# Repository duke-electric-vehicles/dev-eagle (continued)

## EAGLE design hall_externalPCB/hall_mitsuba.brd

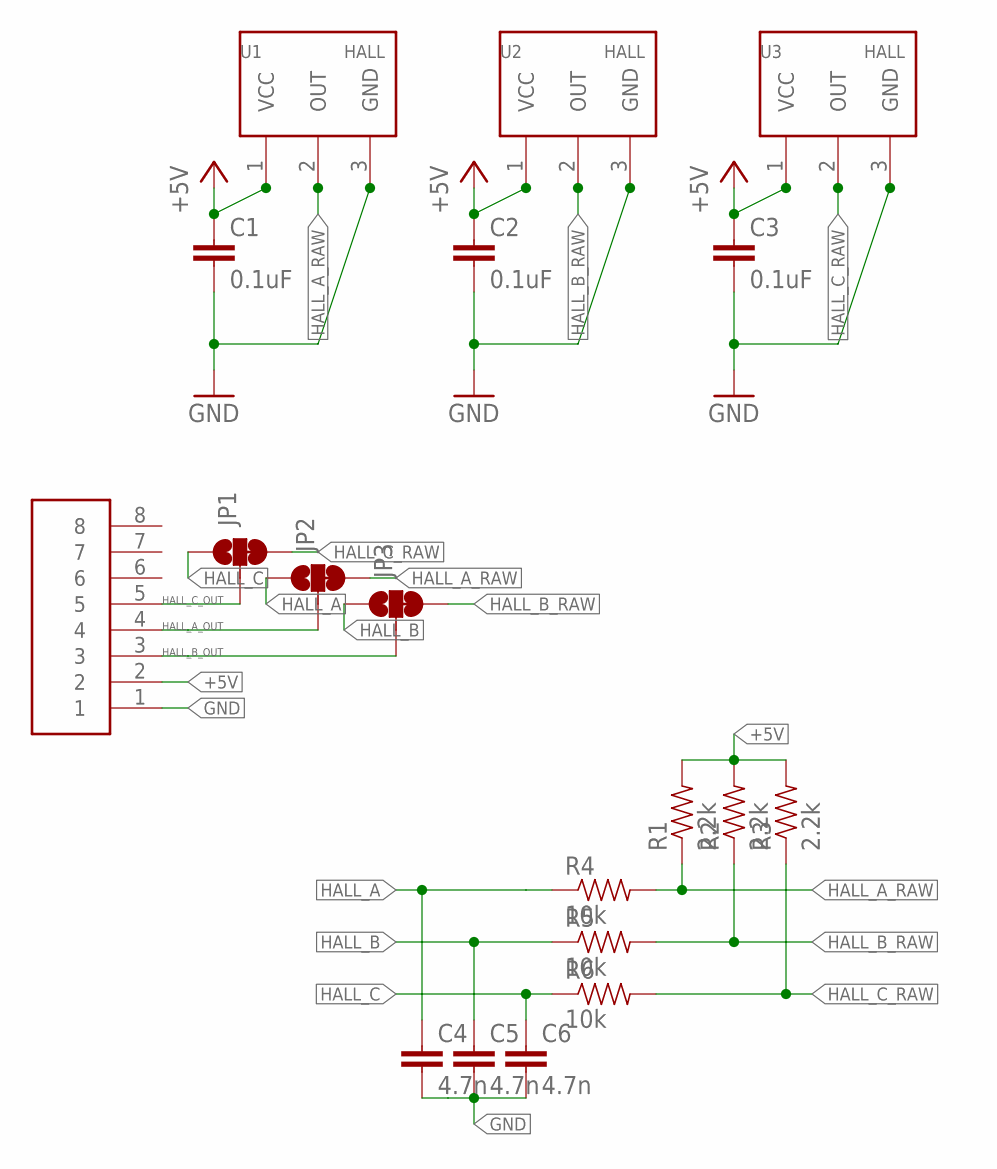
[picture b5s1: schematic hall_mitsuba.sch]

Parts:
C1, C2, C3: 0.1uF; 0603-CAP
C4, C5, C6: 4.7n; 0603-CAP
JP1, JP2, JP3: JUMPER-SMT_3_1-NC_TRACE_SILK; SMT-JUMPER_3_1-NC_TRACE_SILK
R1, R2, R3: 2.2k; 0603-RES
R4, R5, R6: 10k; 0603-RES
U1, U2, U3: HALL_SOT23W; SOT23W
U$1: HEADER8DEFAULT; 8PINVALULOK

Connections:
+5V: C1.1, C2.1, C3.1, R1.2, R2.2, R3.2, U1.1 (VCC), U2.1 (VCC), U3.1 (VCC), U$1.2
GND: C1.2, C2.2, C3.2, C4.2, C5.2, C6.2, U1.3 (GND), U2.3 (GND), U3.3 (GND), U$1.1
HALL_A: C4.1, JP2.1, R4.1
HALL_A_OUT: JP2.2, U$1.4
HALL_A_RAW: JP2.3, R1.1, R4.2, U1.2 (OUT)
HALL_B: C5.1, JP3.1, R5.1
HALL_B_OUT: JP3.2, U$1.3
HALL_B_RAW: JP3.3, R2.1, R5.2, U2.2 (OUT)
HALL_C: C6.1, JP1.1, R6.1
HALL_C_OUT: JP1.2, U$1.5
HALL_C_RAW: JP1.3, R3.1, R6.2, U3.2 (OUT)

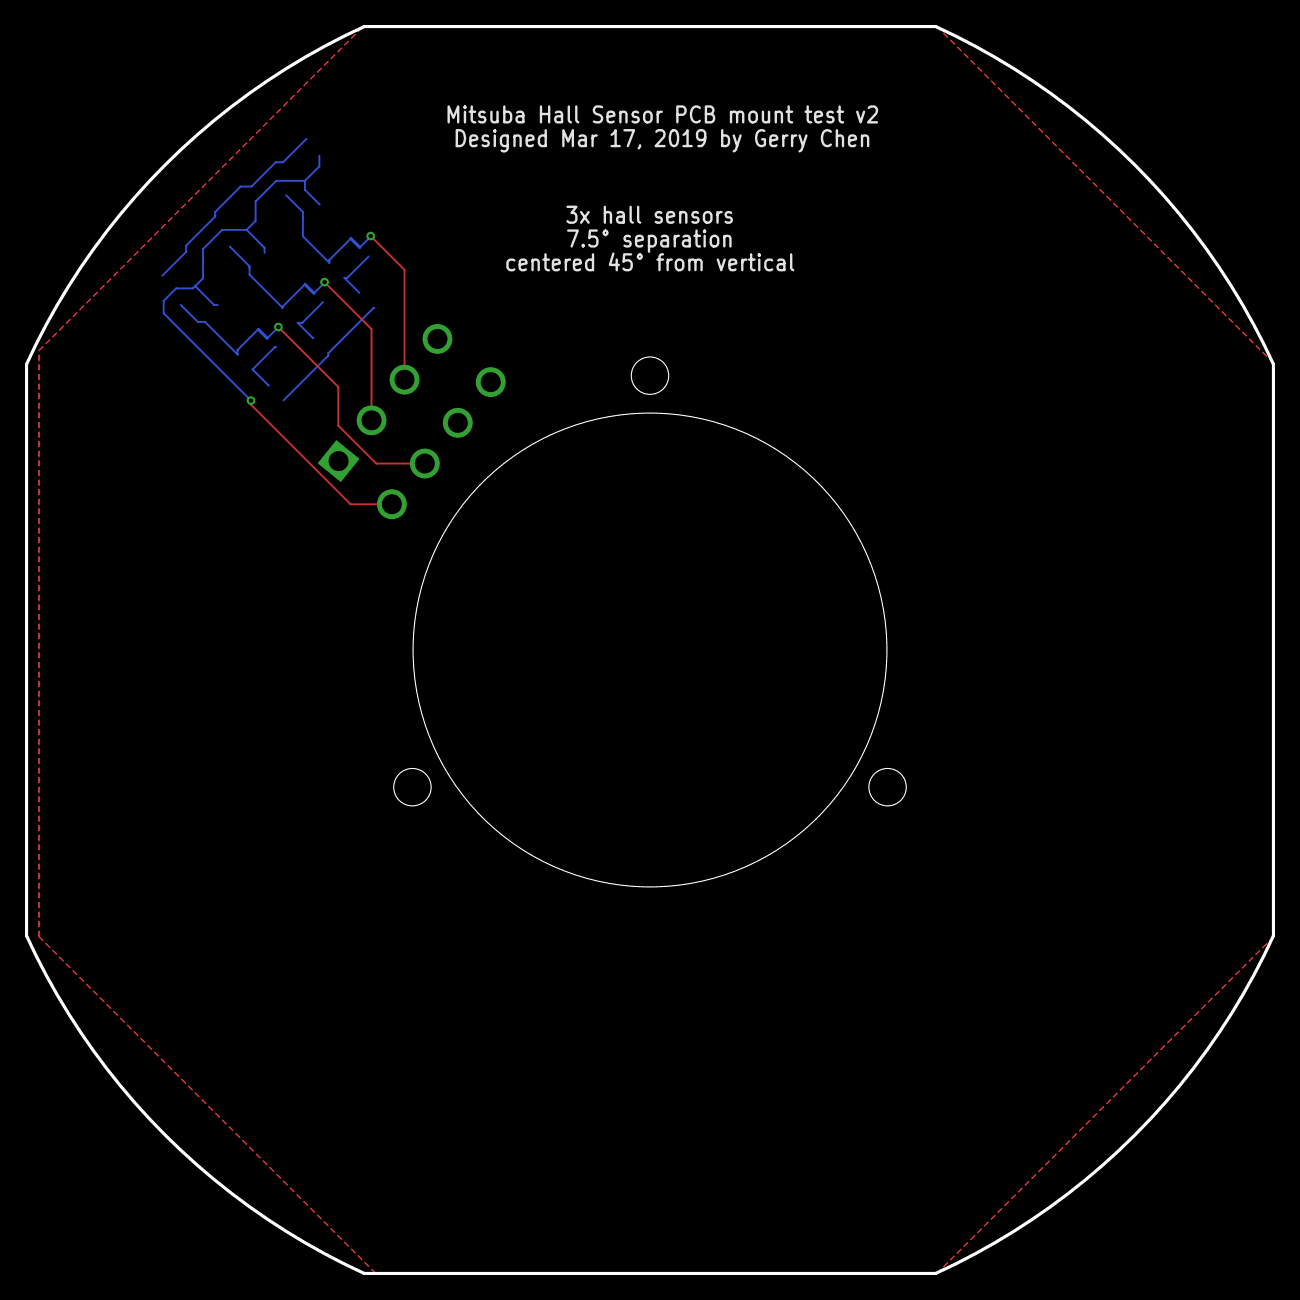
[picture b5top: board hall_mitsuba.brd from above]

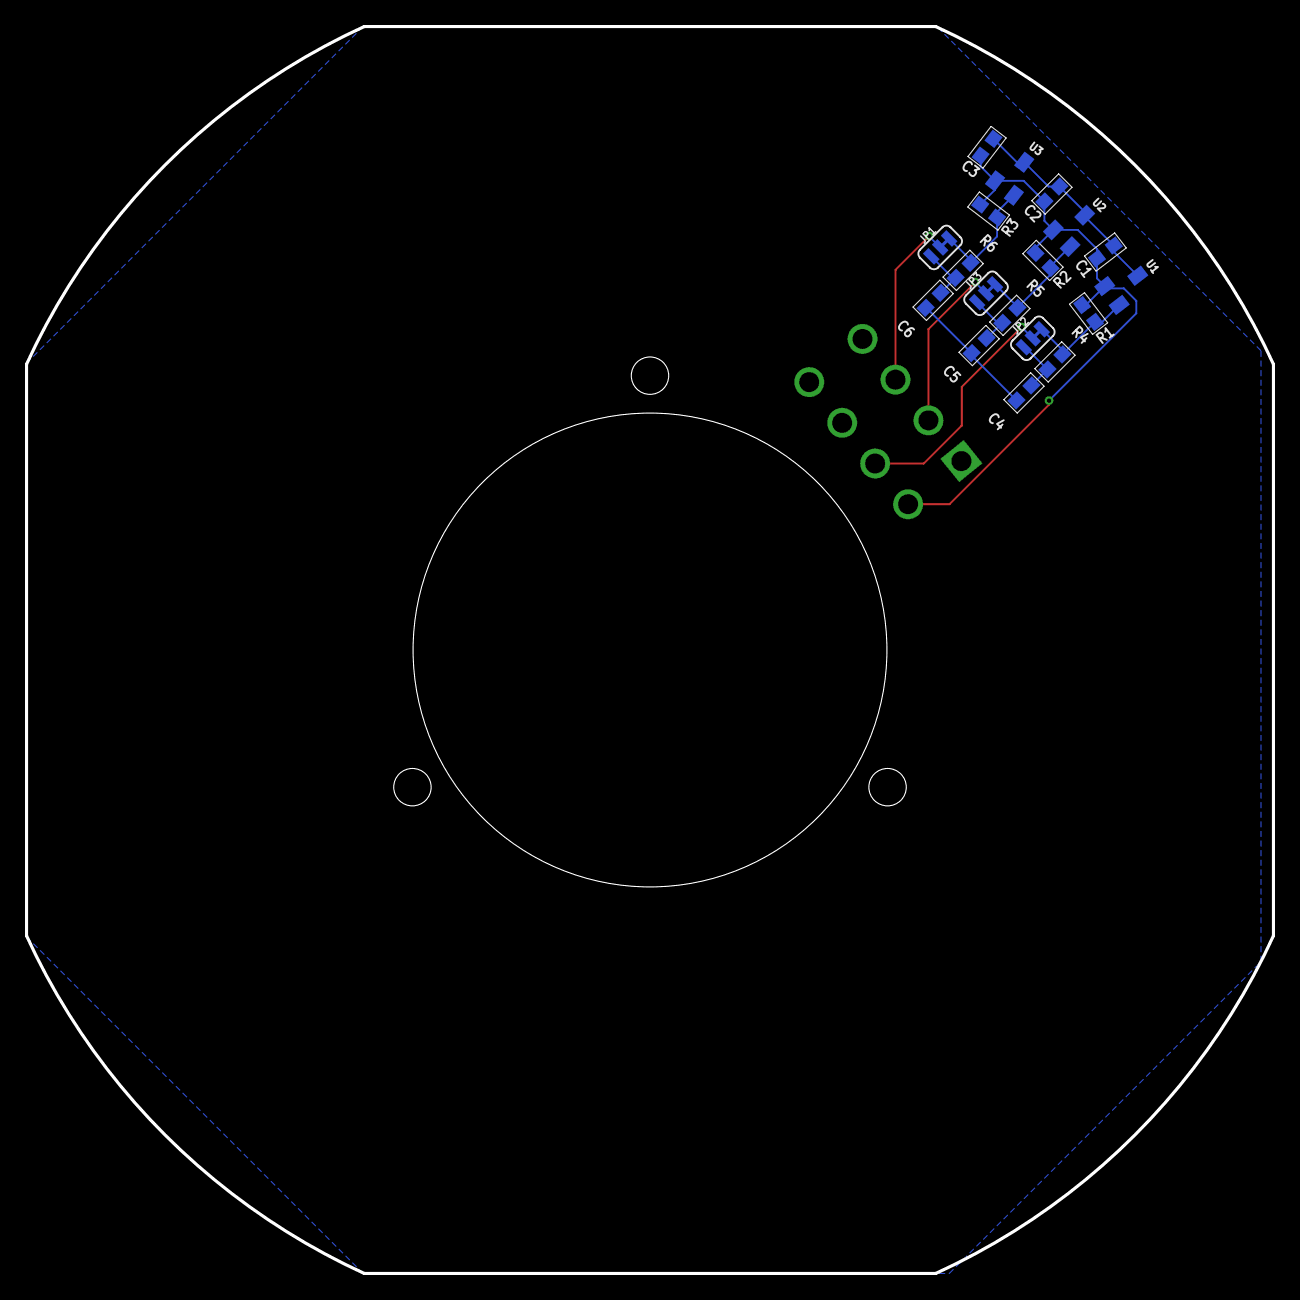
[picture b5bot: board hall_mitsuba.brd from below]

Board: 2 copper layers, 100.0 x 100.0 mm, 21 parts (18 on the bottom side), 11 nets.

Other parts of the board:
U$2, U$3: DEV

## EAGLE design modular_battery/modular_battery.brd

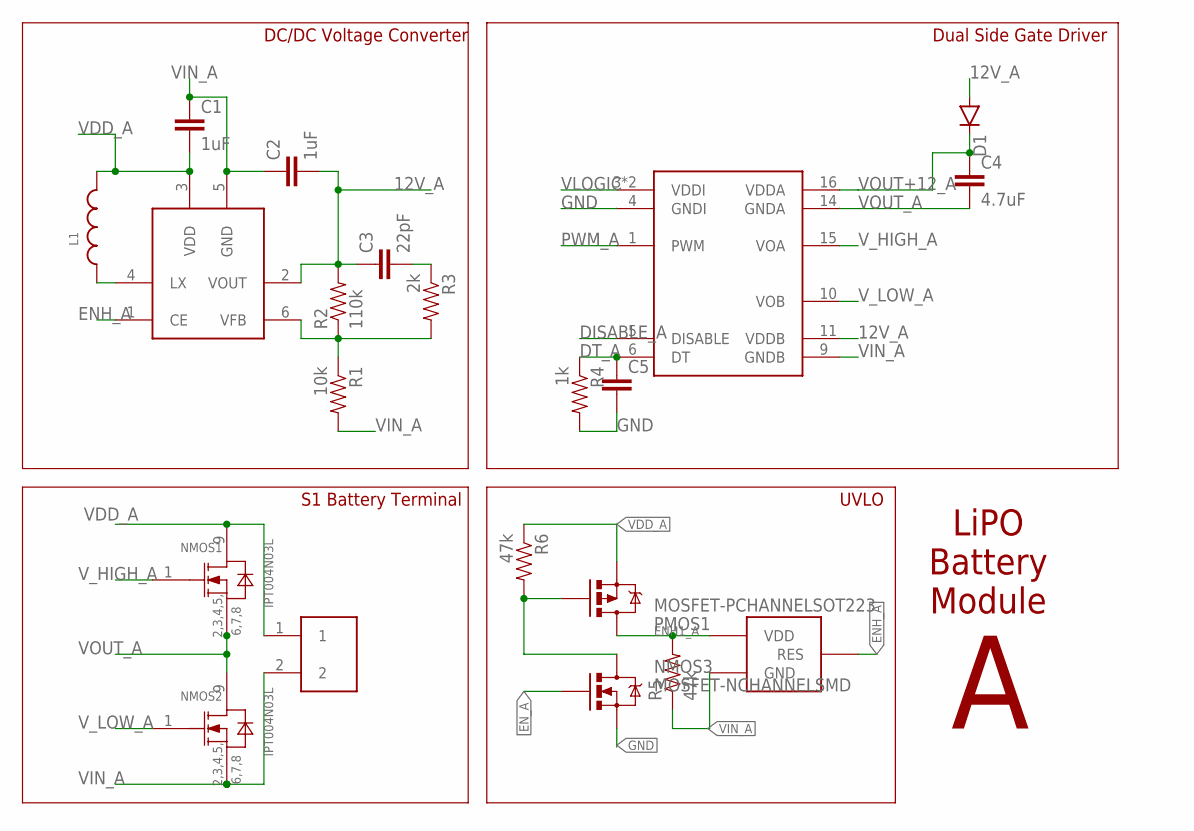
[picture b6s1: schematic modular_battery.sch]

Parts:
C1, C2: 1uF; 0603-CAP
C3: 22pF; 0603-CAP
C4: 4.7uF; 0603-CAP
C5: CAP0603-CAP; 0603-CAP
D1: DIODESMB; SMB-DIODE
DRIVER1: SI8231SOIC16W; SOIC16LWB
L1: WE-LQS_4025_74404043220A; WE-LQS_4025
NMOS1, NMOS2: IPT004N03L; INF-PG-HSOF-8-1-0
NMOS3: MOSFET-NCHANNELSMD; SOT23-3
PMOS1: MOSFET-PCHANNELSOT223; SOT223
R1: 10k; 0603-RES
R2: 110k; 0603-RES
R3: 2k; 0603-RES
R4: 1k; 0603-RES
R5, R6: 47k; 0603-RES
U$3: HEADER2; 2PINVALULOK
VDETECTOR1: BD49XXK__G; SOT23-3
VREG1: R1200SOT-23-6; SOT-23-6

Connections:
12V_A: C2.2, C3.1, D1.A, DRIVER1.11 (VDDB), R2.2, VREG1.2 (VOUT)
DISABLE_A: DRIVER1.5 (DISABLE)
DT_A: C5.1, DRIVER1.6 (DT), R4.1
ENH1_A: PMOS1.2 (D), PMOS1.4 (D), R5.2, VDETECTOR1.3 (VDD)
ENH_A: VDETECTOR1.2 (RES), VREG1.1 (CE)
EN_A: NMOS3.1 (G)
GND: C5.2, DRIVER1.4 (GNDI), NMOS3.2 (S), R4.2
unnamed: L1.1, VREG1.4 (LX)
unnamed: R1.1, R2.1, R3.2, VREG1.6 (VFB)
unnamed: C3.2, R3.1
unnamed: NMOS3.3 (D), PMOS1.1 (G), R6.2
PWM_A: DRIVER1.1 (PWM)
VDD_A: C1.2, L1.2, NMOS1.9, PMOS1.3 (S), R6.1, U$3.1, VREG1.3 (VDD)
VIN_A: C1.1, C2.1, DRIVER1.9 (GNDB), NMOS2.2, NMOS2.3, NMOS2.4, NMOS2.5, NMOS2.6, NMOS2.7, NMOS2.8, R1.2, R5.1, U$3.2, VDETECTOR1.1 (GND), VREG1.5 (GND)
VLOGIC: DRIVER1.3 (VDDI), DRIVER1.8 (VDDI)
VOUT+12_A: C4.1, D1.C, DRIVER1.16 (VDDA)
VOUT_A: C4.2, DRIVER1.14 (GNDA), NMOS1.2, NMOS1.3, NMOS1.4, NMOS1.5, NMOS1.6, NMOS1.7, NMOS1.8, NMOS2.9
V_HIGH_A: DRIVER1.15 (VOA), NMOS1.1
V_LOW_A: DRIVER1.10 (VOB), NMOS2.1

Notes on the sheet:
DC/DC Voltage Converter
S1 Battery Terminal
Dual Side Gate Driver
LiPO Battery Module
UVLO

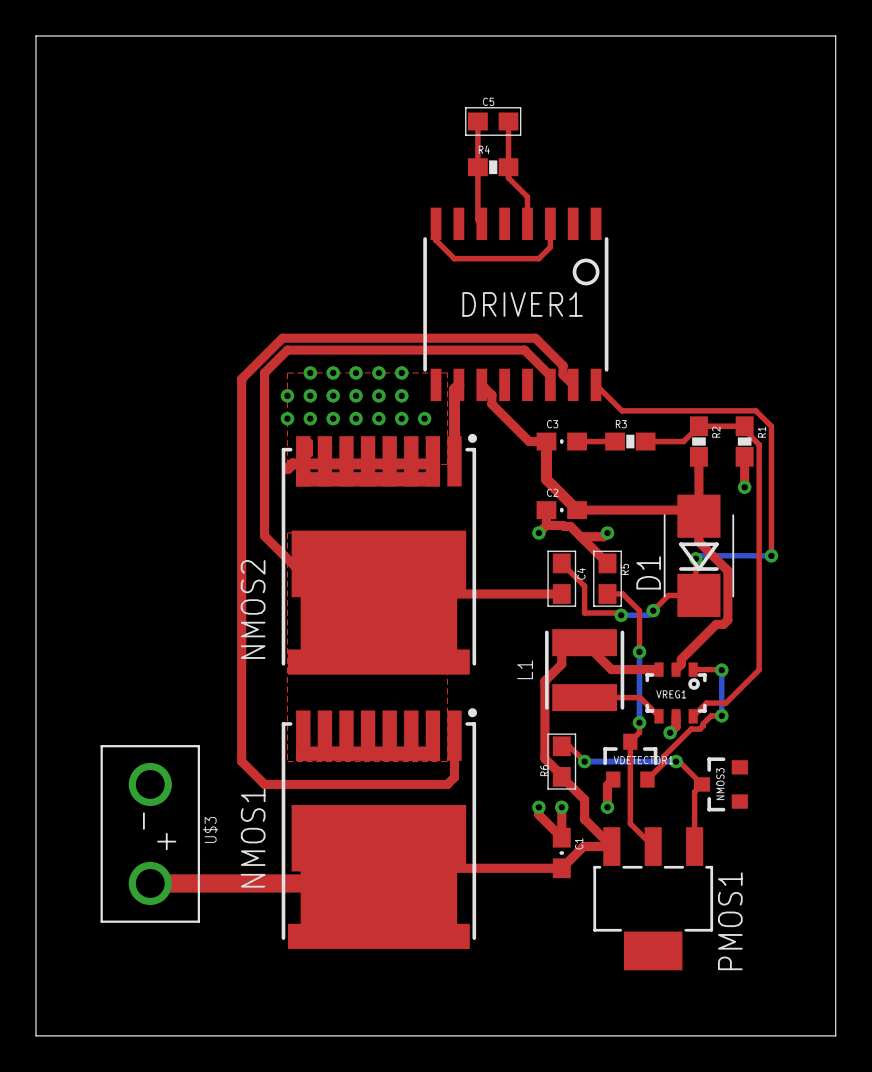
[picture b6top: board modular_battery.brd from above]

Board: 2 copper layers, 44.4 x 55.6 mm, 21 parts (0 on the bottom side), 16 nets.

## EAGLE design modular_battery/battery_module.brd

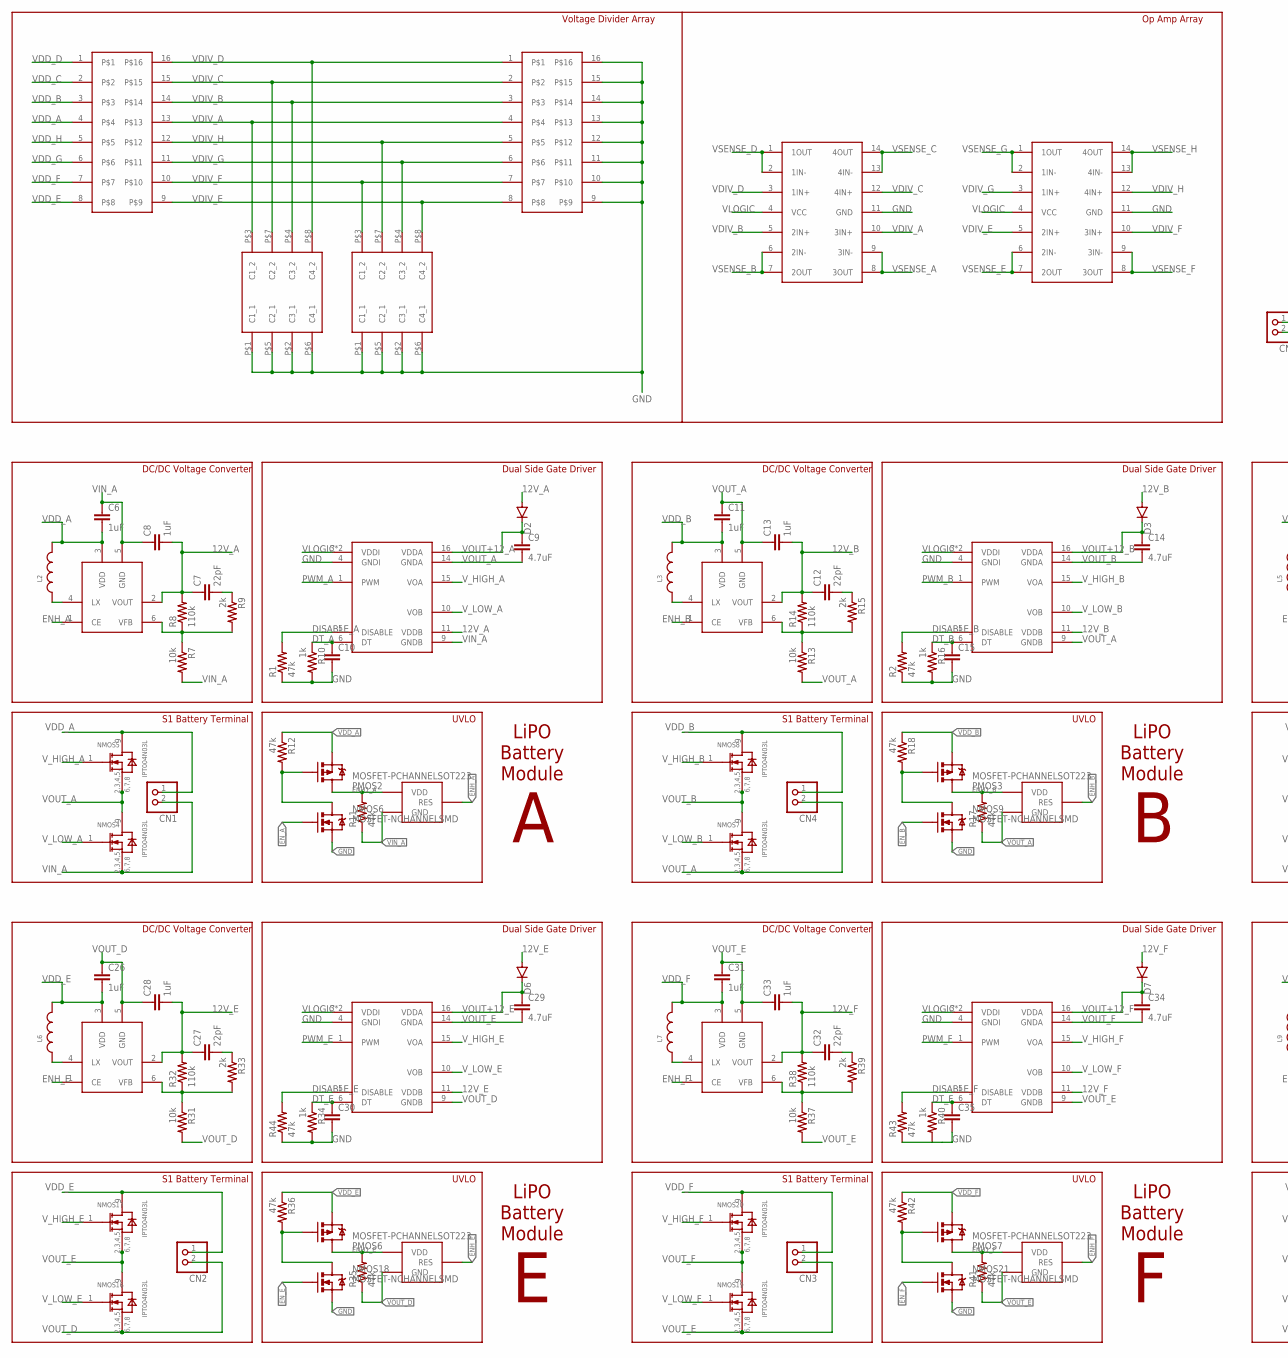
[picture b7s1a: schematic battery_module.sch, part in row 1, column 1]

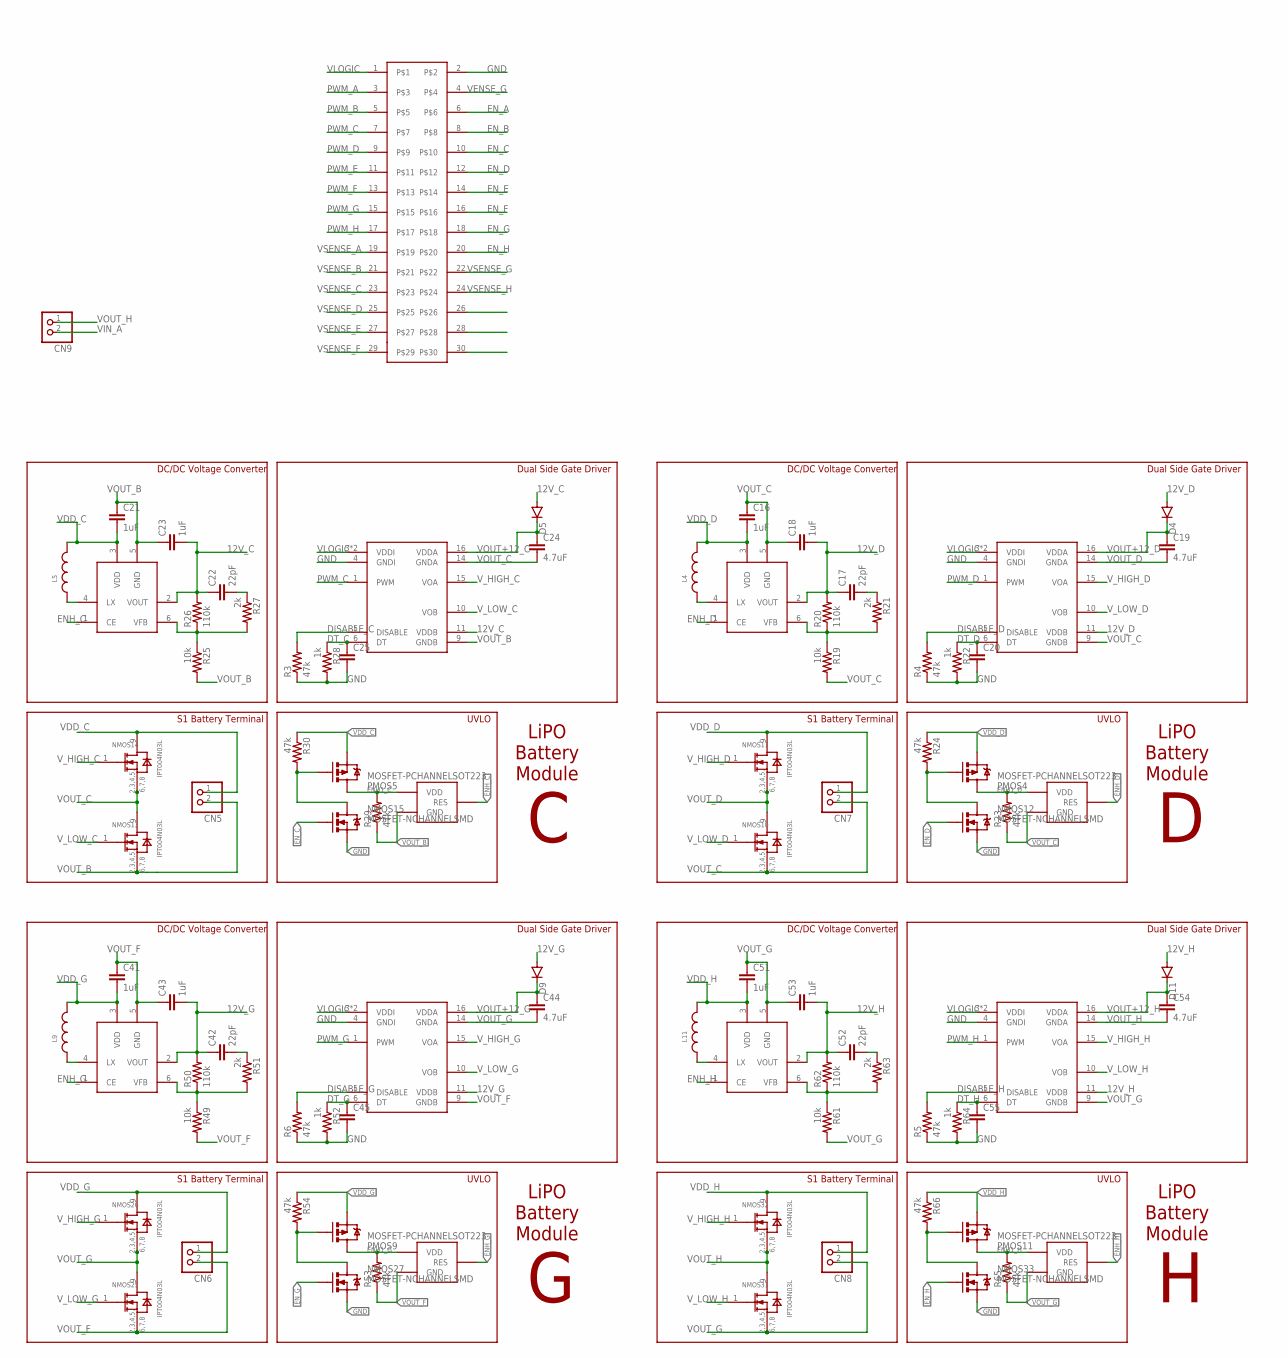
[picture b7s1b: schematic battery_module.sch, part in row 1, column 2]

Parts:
ARRAY1: 47k; 1506
ARRAY2: EXB-2HV; 1506
C6, C8, C11, C13, C16, C18, C21, C23, C26, C28, C31, C33, C41, C43, C51, C53: 1uF; 0603-CAP
C7, C12, C17, C22, C27, C32, C42, C52: 22pF; 0603-CAP
C9, C14, C19, C24, C29, C34, C44, C54: 4.7uF; 0603-CAP
C10, C15, C20, C25, C30, C35, C45, C55: CAP0603-CAP; 0603-CAP
CN1, CN2, CN3, CN4, CN5, CN6, CN7, CN8, CN9: JST_2PIN-THM; JST-PH-2-THM
D2, D3, D4, D5, D6, D7, D9, D11: DIODESMB; SMB-DIODE
DRIVER2, DRIVER3, DRIVER4, DRIVER5, DRIVER6, DRIVER7, DRIVER9, DRIVER11: SI8231SOIC16W; SOIC16LWB
L2, L3, L4, L5, L6, L7, L9, L11: WE-LQS_4025_74404043220A; WE-LQS_4025
NMOS4, NMOS5, NMOS7, NMOS8, NMOS10, NMOS11, NMOS13, NMOS14, NMOS16, NMOS17, NMOS19, NMOS20, NMOS25, NMOS26, NMOS31, NMOS32: IPT004N03L; INF-PG-HSOF-8-1-0
NMOS6, NMOS9, NMOS12, NMOS15, NMOS18, NMOS21, NMOS27, NMOS33: MOSFET-NCHANNELSMD; SOT23-3
PMOS2, PMOS3, PMOS4, PMOS5, PMOS6, PMOS7, PMOS9, PMOS11: MOSFET-PCHANNELSOT223; SOT223
R1, R2, R3, R4, R5, R6, R11, R12, R17, R18, R23, R24, R29, R30, R35, R36, R41, R42, R43, R44, R53, R54, R65, R66: 47k; 0603-RES
R7, R13, R19, R25, R31, R37, R49, R61: 10k; 0603-RES
R8, R14, R20, R26, R32, R38, R50, R62: 110k; 0603-RES
R9, R15, R21, R27, R33, R39, R51, R63: 2k; 0603-RES
R10, R16, R22, R28, R34, R40, R52, R64: 1k; 0603-RES
U$1: 30_HEADER; 2X15_SHROUDED
U$10, U$12: LM324; SOIC14
U$11, U$13: CL31; 1206-4XARRAY
VDETECTOR2, VDETECTOR3, VDETECTOR4, VDETECTOR5, VDETECTOR6, VDETECTOR7, VDETECTOR9, VDETECTOR11: BD49XXK__G; SOT23-3
VREG2, VREG3, VREG4, VREG5, VREG6, VREG7, VREG9, VREG11: R1200SOT-23-6; SOT-23-6

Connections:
12V_A: C7.1, C8.2, D2.A, DRIVER2.11 (VDDB), R8.2, VREG2.2 (VOUT)
12V_B: C12.1, C13.2, D3.A, DRIVER3.11 (VDDB), R14.2, VREG3.2 (VOUT)
12V_C: C22.1, C23.2, D5.A, DRIVER5.11 (VDDB), R26.2, VREG5.2 (VOUT)
12V_D: C17.1, C18.2, D4.A, DRIVER4.11 (VDDB), R20.2, VREG4.2 (VOUT)
12V_E: C27.1, C28.2, D6.A, DRIVER6.11 (VDDB), R32.2, VREG6.2 (VOUT)
12V_F: C32.1, C33.2, D7.A, DRIVER7.11 (VDDB), R38.2, VREG7.2 (VOUT)
12V_G: C42.1, C43.2, D9.A, DRIVER9.11 (VDDB), R50.2, VREG9.2 (VOUT)
12V_H: C52.1, C53.2, D11.A, DRIVER11.11 (VDDB), R62.2, VREG11.2 (VOUT)
DISABLE_A: DRIVER2.5 (DISABLE), R1.2
DISABLE_B: DRIVER3.5 (DISABLE), R2.2
DISABLE_C: DRIVER5.5 (DISABLE), R3.2
DISABLE_D: DRIVER4.5 (DISABLE), R4.2
DISABLE_E: DRIVER6.5 (DISABLE), R44.2
DISABLE_F: DRIVER7.5 (DISABLE), R43.2
DISABLE_G: DRIVER9.5 (DISABLE), R6.2
DISABLE_H: DRIVER11.5 (DISABLE), R5.2
DT_A: C10.1, DRIVER2.6 (DT), R10.1
DT_B: C15.1, DRIVER3.6 (DT), R16.1
DT_C: C25.1, DRIVER5.6 (DT), R28.1
DT_D: C20.1, DRIVER4.6 (DT), R22.1
DT_E: C30.1, DRIVER6.6 (DT), R34.1
DT_F: C35.1, DRIVER7.6 (DT), R40.1
DT_G: C45.1, DRIVER9.6 (DT), R52.1
DT_H: C55.1, DRIVER11.6 (DT), R64.1
ENH1_A: PMOS2.2 (D), PMOS2.4 (D), R11.2, VDETECTOR2.3 (VDD)
ENH1_B: PMOS3.2 (D), PMOS3.4 (D), R17.2, VDETECTOR3.3 (VDD)
ENH1_C: PMOS5.2 (D), PMOS5.4 (D), R29.2, VDETECTOR5.3 (VDD)
ENH1_D: PMOS4.2 (D), PMOS4.4 (D), R23.2, VDETECTOR4.3 (VDD)
ENH1_E: PMOS6.2 (D), PMOS6.4 (D), R35.2, VDETECTOR6.3 (VDD)
ENH1_F: PMOS7.2 (D), PMOS7.4 (D), R41.2, VDETECTOR7.3 (VDD)
ENH1_G: PMOS9.2 (D), PMOS9.4 (D), R53.2, VDETECTOR9.3 (VDD)
ENH1_H: PMOS11.2 (D), PMOS11.4 (D), R65.2, VDETECTOR11.3 (VDD)
ENH_A: VDETECTOR2.2 (RES), VREG2.1 (CE)
ENH_B: VDETECTOR3.2 (RES), VREG3.1 (CE)
ENH_C: VDETECTOR5.2 (RES), VREG5.1 (CE)
ENH_D: VDETECTOR4.2 (RES), VREG4.1 (CE)
ENH_E: VDETECTOR6.2 (RES), VREG6.1 (CE)
ENH_F: VDETECTOR7.2 (RES), VREG7.1 (CE)
ENH_G: VDETECTOR9.2 (RES), VREG9.1 (CE)
ENH_H: VDETECTOR11.2 (RES), VREG11.1 (CE)
EN_A: NMOS6.1 (G), U$1.6
EN_B: NMOS9.1 (G), U$1.8
EN_C: NMOS15.1 (G), U$1.10
EN_D: NMOS12.1 (G), U$1.12
EN_E: NMOS18.1 (G), U$1.14
EN_F: NMOS21.1 (G), U$1.16
EN_G: NMOS27.1 (G), U$1.18
EN_H: NMOS33.1 (G), U$1.20
GND: ARRAY2.9, ARRAY2.10, ARRAY2.11, ARRAY2.12, ARRAY2.13, ARRAY2.14, ARRAY2.15, ARRAY2.16, C10.2, C15.2, C20.2, C25.2, C30.2, C35.2, C45.2, C55.2, DRIVER2.4 (GNDI), DRIVER3.4 (GNDI), DRIVER4.4 (GNDI), DRIVER5.4 (GNDI), DRIVER6.4 (GNDI), DRIVER7.4 (GNDI), DRIVER9.4 (GNDI), DRIVER11.4 (GNDI), NMOS6.2 (S), NMOS9.2 (S), NMOS12.2 (S), NMOS15.2 (S), NMOS18.2 (S), NMOS21.2 (S), NMOS27.2 (S), NMOS33.2 (S), R1.1, R2.1, R3.1, R4.1, R5.1, R6.1, R10.2, R16.2, R22.2, R28.2, R34.2, R40.2, R43.1, R44.1, R52.2, R64.2, U$1.2, U$10.11 (GND), U$11.P$1 (C1_1), U$11.P$2 (C3_1), U$11.P$5 (C2_1), U$11.P$6 (C4_1), U$12.11 (GND), U$13.P$1 (C1_1), U$13.P$2 (C3_1), U$13.P$5 (C2_1), U$13.P$6 (C4_1)
unnamed: R7.1, R8.1, R9.2, VREG2.6 (VFB)
unnamed: L2.1, VREG2.4 (LX)
unnamed: C7.2, R9.1
unnamed: NMOS6.3 (D), PMOS2.1 (G), R12.2
unnamed: R13.1, R14.1, R15.2, VREG3.6 (VFB)
unnamed: L3.1, VREG3.4 (LX)
unnamed: C12.2, R15.1
unnamed: NMOS9.3 (D), PMOS3.1 (G), R18.2
unnamed: R19.1, R20.1, R21.2, VREG4.6 (VFB)
unnamed: L4.1, VREG4.4 (LX)
unnamed: C17.2, R21.1
unnamed: NMOS12.3 (D), PMOS4.1 (G), R24.2
unnamed: R25.1, R26.1, R27.2, VREG5.6 (VFB)
unnamed: L5.1, VREG5.4 (LX)
unnamed: C22.2, R27.1
unnamed: NMOS15.3 (D), PMOS5.1 (G), R30.2
unnamed: R31.1, R32.1, R33.2, VREG6.6 (VFB)
unnamed: L6.1, VREG6.4 (LX)
unnamed: C27.2, R33.1
unnamed: NMOS18.3 (D), PMOS6.1 (G), R36.2
unnamed: R37.1, R38.1, R39.2, VREG7.6 (VFB)
unnamed: L7.1, VREG7.4 (LX)
unnamed: C32.2, R39.1
unnamed: NMOS21.3 (D), PMOS7.1 (G), R42.2
unnamed: R49.1, R50.1, R51.2, VREG9.6 (VFB)
unnamed: L9.1, VREG9.4 (LX)
unnamed: C42.2, R51.1
unnamed: NMOS27.3 (D), PMOS9.1 (G), R54.2
unnamed: R61.1, R62.1, R63.2, VREG11.6 (VFB)
unnamed: L11.1, VREG11.4 (LX)
unnamed: C52.2, R63.1
unnamed: NMOS33.3 (D), PMOS11.1 (G), R66.2
PWM_A: DRIVER2.1 (PWM), U$1.3
PWM_B: DRIVER3.1 (PWM), U$1.5
PWM_C: DRIVER5.1 (PWM), U$1.7
PWM_D: DRIVER4.1 (PWM), U$1.9
PWM_E: DRIVER6.1 (PWM), U$1.11
PWM_F: DRIVER7.1 (PWM), U$1.13
PWM_G: DRIVER9.1 (PWM), U$1.15
PWM_H: DRIVER11.1 (PWM), U$1.17
VDD_A: ARRAY1.4, C6.2, CN1.1 (2), L2.2, NMOS5.9, PMOS2.3 (S), R12.1, VREG2.3 (VDD)
VDD_B: ARRAY1.3, C11.2, CN4.1 (2), L3.2, NMOS8.9, PMOS3.3 (S), R18.1, VREG3.3 (VDD)
VDD_C: ARRAY1.2, C21.2, CN5.1 (2), L5.2, NMOS14.9, PMOS5.3 (S), R30.1, VREG5.3 (VDD)
VDD_D: ARRAY1.1, C16.2, CN7.1 (2), L4.2, NMOS11.9, PMOS4.3 (S), R24.1, VREG4.3 (VDD)
VDD_E: ARRAY1.8, C26.2, CN2.1 (2), L6.2, NMOS17.9, PMOS6.3 (S), R36.1, VREG6.3 (VDD)
VDD_F: ARRAY1.7, C31.2, CN3.1 (2), L7.2, NMOS20.9, PMOS7.3 (S), R42.1, VREG7.3 (VDD)
VDD_G: ARRAY1.6, C41.2, CN6.1 (2), L9.2, NMOS26.9, PMOS9.3 (S), R54.1, VREG9.3 (VDD)
VDD_H: ARRAY1.5, C51.2, CN8.1 (2), L11.2, NMOS32.9, PMOS11.3 (S), R66.1, VREG11.3 (VDD)
VDIV_A: ARRAY1.13, ARRAY2.4, U$11.P$3 (C1_2), U$12.10 (3IN+)
VDIV_B: ARRAY1.14, ARRAY2.3, U$11.P$4 (C3_2), U$12.5 (2IN+)
VDIV_C: ARRAY1.15, ARRAY2.2, U$11.P$7 (C2_2), U$12.12 (4IN+)
VDIV_D: ARRAY1.16, ARRAY2.1, U$11.P$8 (C4_2), U$12.3 (1IN+)
VDIV_E: ARRAY1.9, ARRAY2.8, U$10.5 (2IN+), U$13.P$8 (C4_2)
VDIV_F: ARRAY1.10, ARRAY2.7, U$10.10 (3IN+), U$13.P$3 (C1_2)
VDIV_G: ARRAY1.11, ARRAY2.6, U$10.3 (1IN+), U$13.P$4 (C3_2)
VDIV_H: ARRAY1.12, ARRAY2.5, U$10.12 (4IN+), U$13.P$7 (C2_2)
VENSE_G: U$1.4
VIN_A: C6.1, C8.1, CN1.2 (1), CN9.2 (1), DRIVER2.9 (GNDB), NMOS4.2, NMOS4.3, NMOS4.4, NMOS4.5, NMOS4.6, NMOS4.7, NMOS4.8, R7.2, R11.1, VDETECTOR2.1 (GND), VREG2.5 (GND); also elsewhere on the board
VLOGIC: DRIVER2.3 (VDDI), DRIVER2.8 (VDDI), DRIVER3.3 (VDDI), DRIVER3.8 (VDDI), DRIVER4.3 (VDDI), DRIVER4.8 (VDDI), DRIVER5.3 (VDDI), DRIVER5.8 (VDDI), DRIVER6.3 (VDDI), DRIVER6.8 (VDDI), DRIVER7.3 (VDDI), DRIVER7.8 (VDDI), DRIVER9.3 (VDDI), DRIVER9.8 (VDDI), DRIVER11.3 (VDDI), DRIVER11.8 (VDDI), U$1.1, U$10.4 (VCC), U$12.4 (VCC)
VOUT+12_A: C9.1, D2.C, DRIVER2.16 (VDDA)
VOUT+12_B: C14.1, D3.C, DRIVER3.16 (VDDA)
VOUT+12_C: C24.1, D5.C, DRIVER5.16 (VDDA)
VOUT+12_D: C19.1, D4.C, DRIVER4.16 (VDDA)
VOUT+12_E: C29.1, D6.C, DRIVER6.16 (VDDA)
VOUT+12_F: C34.1, D7.C, DRIVER7.16 (VDDA)
VOUT+12_G: C44.1, D9.C, DRIVER9.16 (VDDA)
VOUT+12_H: C54.1, D11.C, DRIVER11.16 (VDDA)
VOUT_A: C9.2, C11.1, C13.1, CN4.2 (1), DRIVER2.14 (GNDA), DRIVER3.9 (GNDB), NMOS4.9, NMOS5.2, NMOS5.3, NMOS5.4, NMOS5.5, NMOS5.6, NMOS5.7, NMOS5.8, NMOS7.2, NMOS7.3, NMOS7.4, NMOS7.5, NMOS7.6, NMOS7.7, NMOS7.8, R13.2, R17.1, VDETECTOR3.1 (GND), VREG3.5 (GND)
VOUT_B: C14.2, C21.1, C23.1, CN5.2 (1), DRIVER3.14 (GNDA), DRIVER5.9 (GNDB), NMOS7.9, NMOS8.2, NMOS8.3, NMOS8.4, NMOS8.5, NMOS8.6, NMOS8.7, NMOS8.8, NMOS13.2, NMOS13.3, NMOS13.4, NMOS13.5, NMOS13.6, NMOS13.7, NMOS13.8, R25.2, R29.1, VDETECTOR5.1 (GND), VREG5.5 (GND)
VOUT_C: C16.1, C18.1, C24.2, CN7.2 (1), DRIVER4.9 (GNDB), DRIVER5.14 (GNDA), NMOS10.2, NMOS10.3, NMOS10.4, NMOS10.5, NMOS10.6, NMOS10.7, NMOS10.8, NMOS13.9, NMOS14.2, NMOS14.3, NMOS14.4, NMOS14.5, NMOS14.6, NMOS14.7, NMOS14.8, R19.2, R23.1, VDETECTOR4.1 (GND), VREG4.5 (GND)
VOUT_D: C19.2, C26.1, C28.1, CN2.2 (1), DRIVER4.14 (GNDA), DRIVER6.9 (GNDB), NMOS10.9, NMOS11.2, NMOS11.3, NMOS11.4, NMOS11.5, NMOS11.6, NMOS11.7, NMOS11.8, NMOS16.2, NMOS16.3, NMOS16.4, NMOS16.5, NMOS16.6, NMOS16.7, NMOS16.8, R31.2, R35.1, VDETECTOR6.1 (GND), VREG6.5 (GND)
VOUT_E: C29.2, C31.1, C33.1, CN3.2 (1), DRIVER6.14 (GNDA), DRIVER7.9 (GNDB), NMOS16.9, NMOS17.2, NMOS17.3, NMOS17.4, NMOS17.5, NMOS17.6, NMOS17.7, NMOS17.8, NMOS19.2, NMOS19.3, NMOS19.4, NMOS19.5, NMOS19.6, NMOS19.7, NMOS19.8, R37.2, R41.1, VDETECTOR7.1 (GND), VREG7.5 (GND)
VOUT_F: C34.2, C41.1, C43.1, CN6.2 (1), DRIVER7.14 (GNDA), DRIVER9.9 (GNDB), NMOS19.9, NMOS20.2, NMOS20.3, NMOS20.4, NMOS20.5, NMOS20.6, NMOS20.7, NMOS20.8, NMOS25.2, NMOS25.3, NMOS25.4, NMOS25.5, NMOS25.6, NMOS25.7, NMOS25.8, R49.2, R53.1, VDETECTOR9.1 (GND), VREG9.5 (GND)
VOUT_G: C44.2, C51.1, C53.1, CN8.2 (1), DRIVER9.14 (GNDA), DRIVER11.9 (GNDB), NMOS25.9, NMOS26.2, NMOS26.3, NMOS26.4, NMOS26.5, NMOS26.6, NMOS26.7, NMOS26.8, NMOS31.2, NMOS31.3, NMOS31.4, NMOS31.5, NMOS31.6, NMOS31.7, NMOS31.8, R61.2, R65.1, VDETECTOR11.1 (GND), VREG11.5 (GND)
VOUT_H: C54.2, CN9.1 (2), DRIVER11.14 (GNDA), NMOS31.9, NMOS32.2, NMOS32.3, NMOS32.4, NMOS32.5, NMOS32.6, NMOS32.7, NMOS32.8; also elsewhere on the board
VSENSE_A: U$1.19, U$12.8 (3OUT), U$12.9 (3IN-)
VSENSE_B: U$1.21, U$12.6 (2IN-), U$12.7 (2OUT)
VSENSE_C: U$1.23, U$12.13 (4IN-), U$12.14 (4OUT)
VSENSE_D: U$1.25, U$12.1 (1OUT), U$12.2 (1IN-)
VSENSE_E: U$1.27, U$10.6 (2IN-), U$10.7 (2OUT)
VSENSE_F: U$1.29, U$10.8 (3OUT), U$10.9 (3IN-)
VSENSE_G: U$1.22, U$10.1 (1OUT), U$10.2 (1IN-)
VSENSE_H: U$1.24, U$10.13 (4IN-), U$10.14 (4OUT)
V_HIGH_A: DRIVER2.15 (VOA), NMOS5.1
V_HIGH_B: DRIVER3.15 (VOA), NMOS8.1
V_HIGH_C: DRIVER5.15 (VOA), NMOS14.1
V_HIGH_D: DRIVER4.15 (VOA), NMOS11.1
V_HIGH_E: DRIVER6.15 (VOA), NMOS17.1
V_HIGH_F: DRIVER7.15 (VOA), NMOS20.1
V_HIGH_G: DRIVER9.15 (VOA), NMOS26.1
V_HIGH_H: DRIVER11.15 (VOA), NMOS32.1
V_LOW_A: DRIVER2.10 (VOB), NMOS4.1
V_LOW_B: DRIVER3.10 (VOB), NMOS7.1
V_LOW_C: DRIVER5.10 (VOB), NMOS13.1
V_LOW_D: DRIVER4.10 (VOB), NMOS10.1
V_LOW_E: DRIVER6.10 (VOB), NMOS16.1
V_LOW_F: DRIVER7.10 (VOB), NMOS19.1
V_LOW_G: DRIVER9.10 (VOB), NMOS25.1
V_LOW_H: DRIVER11.10 (VOB), NMOS31.1

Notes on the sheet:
Voltage Divider Array
Op Amp Array
DC/DC Voltage Converter
S1 Battery Terminal
Dual Side Gate Driver
LiPO Battery Module
UVLO

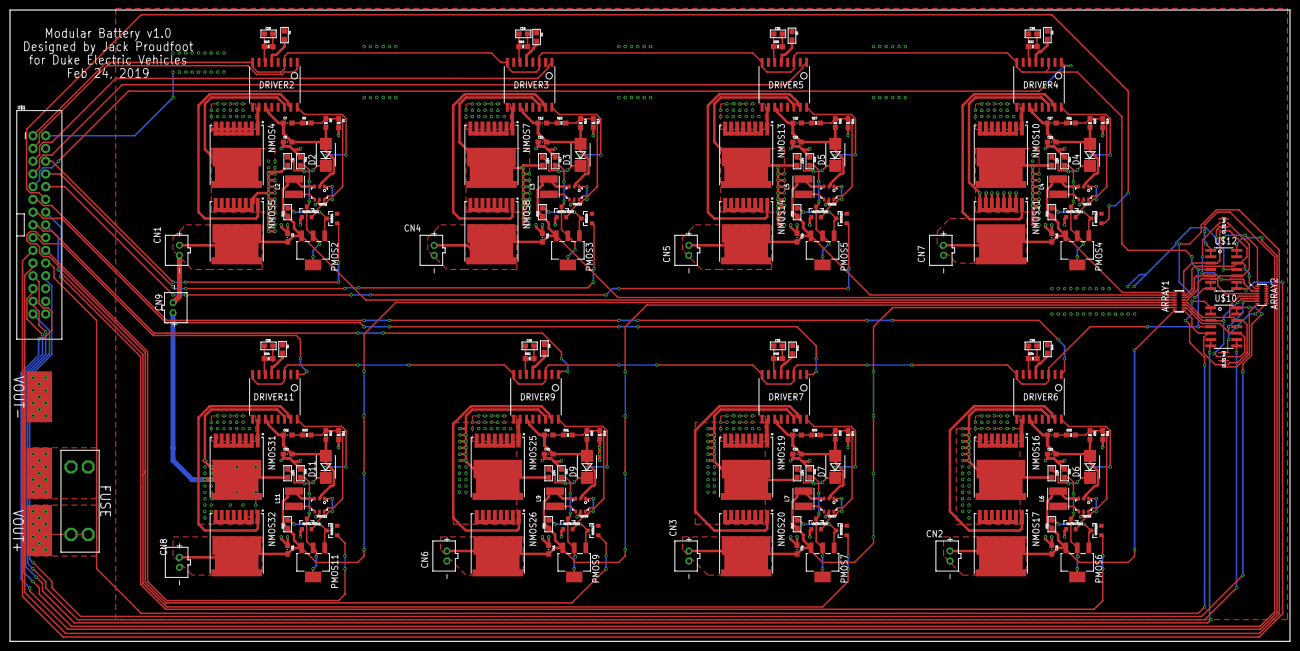
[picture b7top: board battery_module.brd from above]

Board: 2 copper layers, 255.3 x 125.9 mm, 189 parts (0 on the bottom side), 148 nets.

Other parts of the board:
U$2: FUSE; AUTO_FUSE
U$3: DEV
VOUT+: PAD
VOUT-: PAD
VOUT_FUSED: PAD

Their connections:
VIN_A: VOUT-.PAD; also elsewhere on the board
VOUT_FUSED: U$2.2A, U$2.2B, VOUT_FUSED.PAD
VOUT_H: U$2.1A, U$2.1B, VOUT+.PAD; also elsewhere on the board

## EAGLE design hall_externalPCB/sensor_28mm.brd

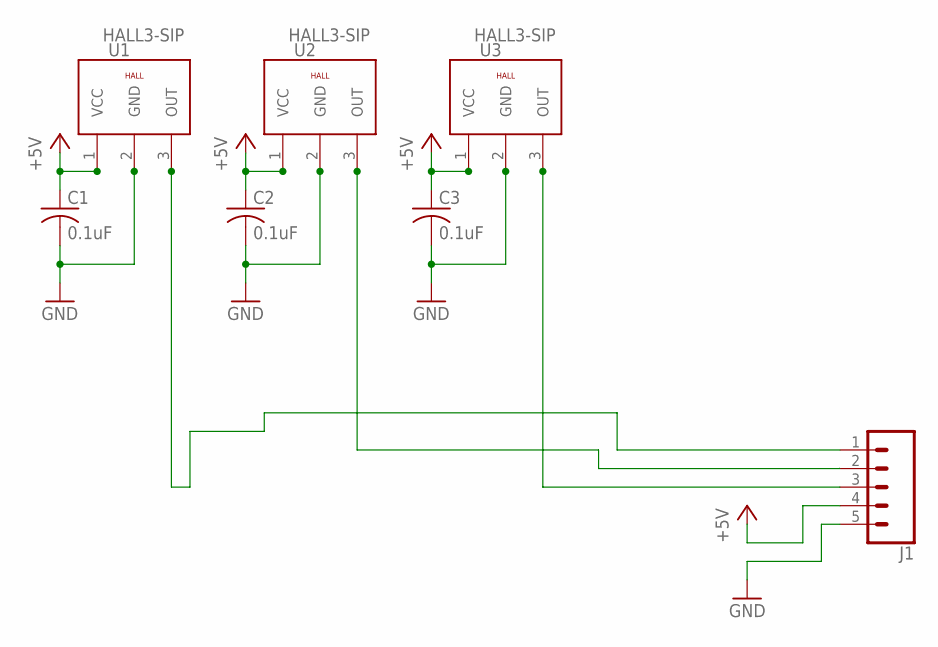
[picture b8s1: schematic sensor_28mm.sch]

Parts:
C1, C2, C3: 0.1uF; C0603
J1: CONN_05PTH_LONGPADS; 1X05_LONGPADS
U1, U2, U3: HALL3-SIP; 3PINS1,27

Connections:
+5V: C1.1, C2.1, C3.1, J1.4, U1.1 (VCC), U2.1 (VCC), U3.1 (VCC)
GND: C1.2, C2.2, C3.2, J1.5, U1.2 (GND), U2.2 (GND), U3.2 (GND)
unnamed: J1.1, U1.3 (OUT)
unnamed: J1.3, U3.3 (OUT)
unnamed: J1.2, U2.3 (OUT)

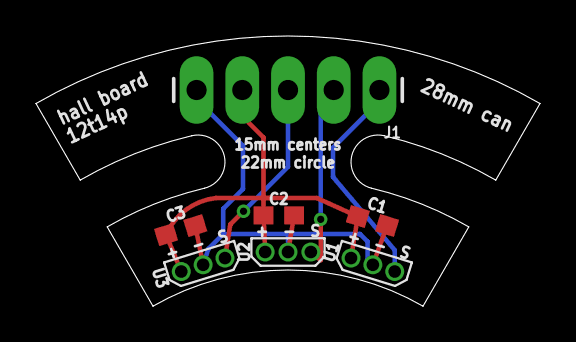
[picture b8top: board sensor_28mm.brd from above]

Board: 2 copper layers, 28.0 x 15.0 mm, 7 parts (0 on the bottom side), 5 nets.

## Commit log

2018-05-31 Added eagle template git ignore
2018-05-31 commit one
2018-05-31 remove gitignore
2018-05-31 Added gitignore take 2
2018-05-31 Added non-conflicting libraries
2018-05-31 Added potentially conflicting libraries uh oh
2018-05-31 more libs
2018-05-31 Added H2v4
2018-06-01 Daily updates. Schematic done, board mostly done
2018-06-01 First rev of h2v4 finished
2018-06-01 Added 2017 controller
2018-06-01 Added BMSs and 2018 controller
2018-06-01 Final
2018-06-01 Added finished gerbers
2018-06-02 Fixed CAM file, and added new gerbers in a zip
2018-06-10 Added final submit gerbers
2018-06-21 Updated controller values to be more realistic
2018-10-05 Added teensy shield for nrf24
    Created a teensy shields directory and added a shield for the teensy 3.2 for an nrf24 radio.
2018-10-05 clean up and CAM job
2018-10-06 Added teensy shield for MPU6050
    Added schematic and board for teensy shield for MPU6050
2018-10-06 Added shield for MPU6050 IC
    Added teensy shield for the MPU6050 IC
2018-10-07 **DS_STORE
2018-10-07 components moved, via example, design version/credit
2018-10-07 Cleaned up board
    Added a pulldown resistor to the i2c channel select pin and cleaned up the the board.
2018-10-07 Switched files
    Corrected file directories
2018-10-07 clean up
2018-10-07 tented vias
2018-10-07 DEV logo
2018-10-09 gerber
2018-10-28 added CAN shield
2018-11-02 Modifed Motor Controller
    Modified 2017 motor controller for better PWM control.
2018-11-06 updated CAN shield
2018-11-06 Added CAN Transceiver
    Added CAN Transceiver to 2019 Motor Controller. Did not update board
2018-11-06 route fixes, routed CAN transciever
2018-11-06 cleanup
2018-11-06 added CAN transceiver
2018-11-07 final boards sent to JLCPCB
2018-11-09 boost converter for historical reasons
2018-12-22 DRU and CAM utilities
2019-01-15 28mm can - arc only (full circle in progress)
2019-02-01 don't know if anything changed but just committing just in case
2019-02-01 Added breakout board for ATF22 pld
    Breakout board for ATF22 pld for mounting to teensy footprint.
2019-02-02 Battery module schematic
    Schematic for single battery module. Contains connection for LiPO battery, two switching mosfets, a gate driver, and dc/dc converter. Multiple modules can be chained together for higher voltages.
2019-02-03 Update battery_module.sch
    Added bootstrap capacitor to high side mosfet driver.
2019-02-04 boot strap and boost converter fixes
2019-02-04 v1.0 Hall board
2019-02-06 Layout for Modular Battery
    Updated schematic for individual battery module and began layout for eight cell modular battery.
2019-02-07 1206 array footprint
2019-02-08 Added FET control for CE
2019-02-10 added UV supervisor - mosfets look good, copied to modular_battery schematic - i guess you need to recopy it back or something later
2019-02-10 forgot to clean up experiments in battery_module
2019-02-18 moved PLD breakout folder
2019-02-18 layout for mitsuba Halls
2019-02-18 placed 8-pin connector
2019-02-20 fixed pass mosfet
2019-02-20 Board layout
    Updated schematic and layed out most of board. Still need to add 30 pin connector.
2019-02-20 new BMS with CAN and NRF24 radio
2019-02-20 routed halls - TODO: sensorless voltage dividers
2019-02-22 final board layout?
2019-02-24 cleanup and CAM
2019-02-24 mitsuba hall CAM first pass test
2019-03-06 notes about changes
2019-03-17 modified external hall mitsuba and also started on internal mitsuba controller
2019-05-04 sensorless ESC based on Patrick's thru hole ESC
2019-05-16 Added joulemeter
2019-05-18 Joulemeter submit
2019-08-19 idk cleanup
